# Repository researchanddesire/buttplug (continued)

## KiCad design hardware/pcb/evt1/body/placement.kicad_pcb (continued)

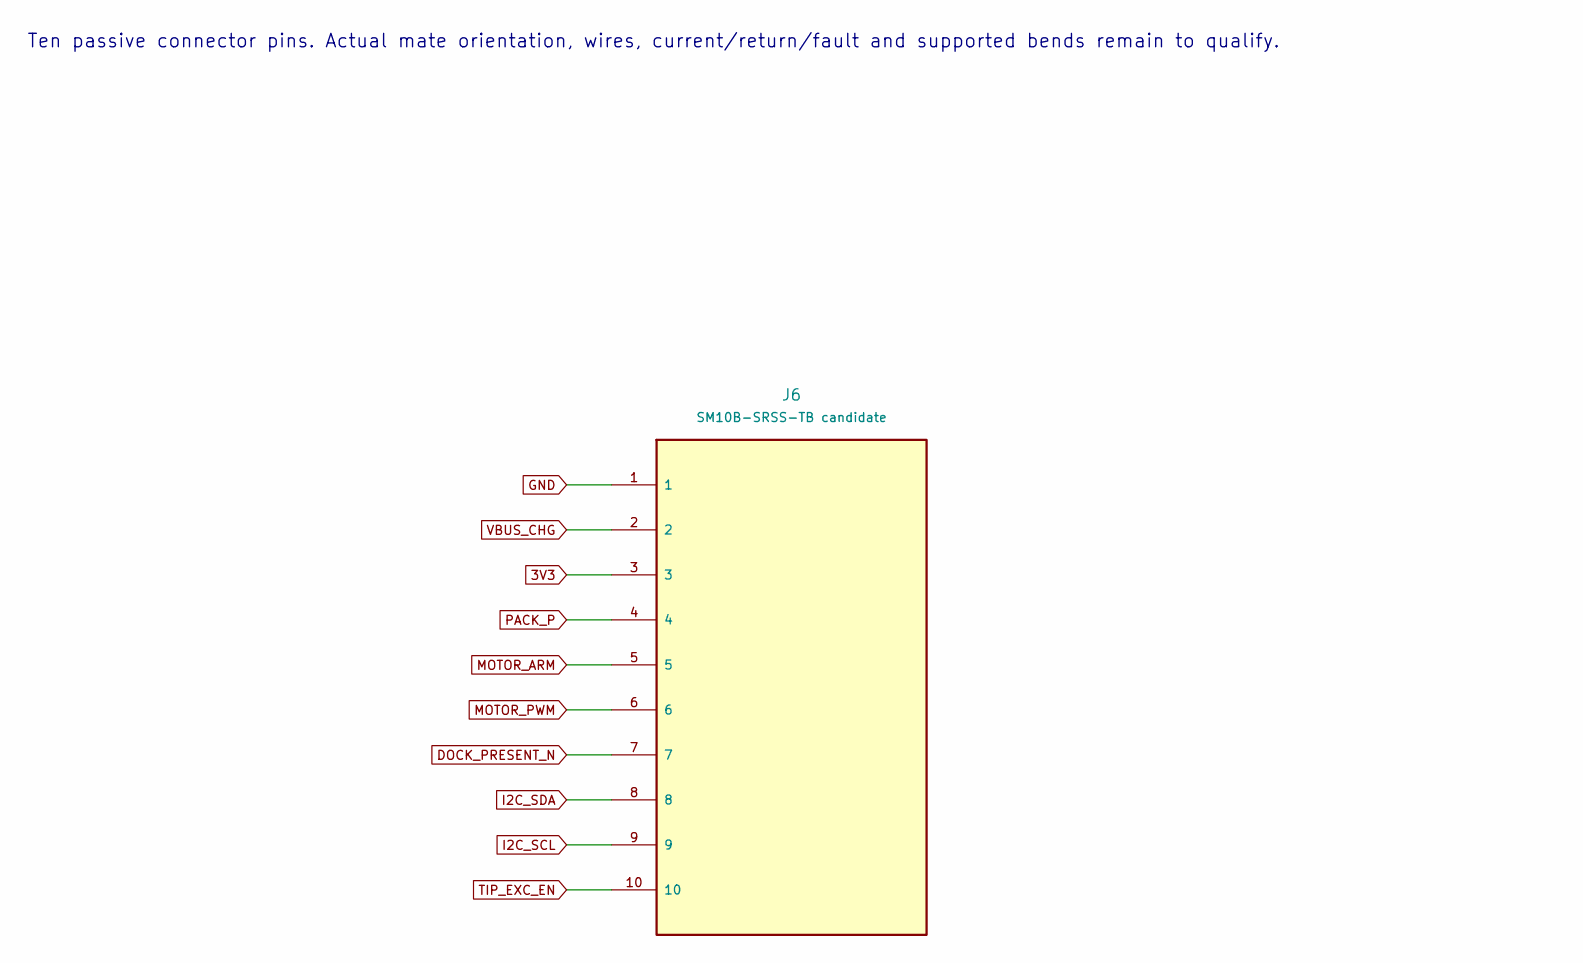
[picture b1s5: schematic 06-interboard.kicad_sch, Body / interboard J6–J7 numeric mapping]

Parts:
J6: SM10B-SRSS-TB candidate; JST_SH_SM10B-SRSS-TB_1x10-1MP_P1.00mm_Horizontal

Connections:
3V3: J6.3; also elsewhere on the board
DOCK_PRESENT_N: J6.7; also elsewhere on the board
GND: J6.1; also elsewhere on the board
I2C_SCL: J6.9; also elsewhere on the board
I2C_SDA: J6.8; also elsewhere on the board
MOTOR_ARM: J6.5; also elsewhere on the board
MOTOR_PWM: J6.6; also elsewhere on the board
PACK_P: J6.4; also elsewhere on the board
TIP_EXC_EN: J6.10; also elsewhere on the board
VBUS_CHG: J6.2; also elsewhere on the board

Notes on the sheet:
Ten passive connector pins. Actual mate orientation, wires, current/return/fault and supported bends remain to qualify.

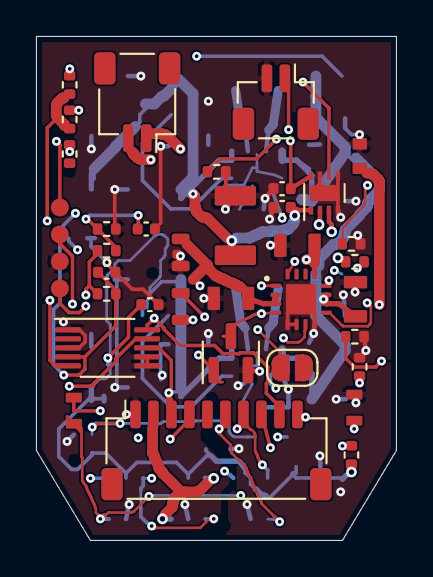
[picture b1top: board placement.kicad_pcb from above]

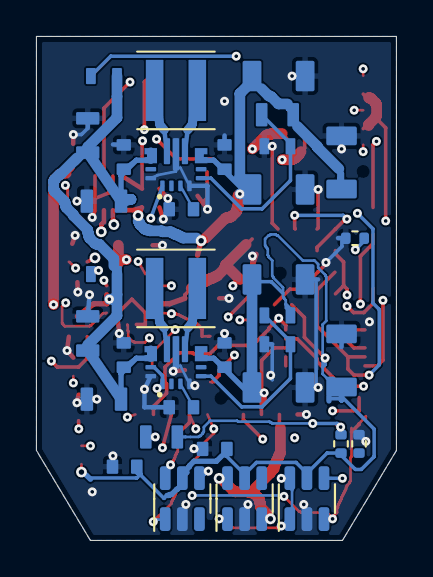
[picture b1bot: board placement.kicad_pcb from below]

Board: 6 copper layers, 20.0 x 28.0 mm, 69 parts (35 on the bottom side), 38 nets.

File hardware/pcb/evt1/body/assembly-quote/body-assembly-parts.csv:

Manufacturer,MPN,Quantity_per_board,References,Schematic_value,Footprint,Assembly_note,Manufacturer_source
Alpha and Omega Semiconductor,AO3400A,1,Q1,AO3400A,PrototypeR0:SOT-23,,https://www.aosmd.com/sites/default/files/res/datasheets/AO3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
Coilcraft,XFL4020-152MEC,2,L1 L2,1.5uH / Isat>=4A candidate,PrototypeR0:L_Coilcraft_XxL4020,Isat is specified at25C. Check transient/current/thermal behavior on assembled regulators; use manufacturer land pattern.,https://www.coilcraft.com/getmedia/50632d43-da1b-4cdb-8ab4-3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
JST,BM02B-SRSS-TB(LF)(SN),1,J5,TIP NTC / GND,EVT1:JST_SH_BM02B-SRSS-TB_1x02-1MP_P1.00mm_Vertical,Board header only. Order matching SHR housings/SSH terminals or qualified precrimp leads separately; flange ends are housed only after feeding free terminals through the neck.,https://www.jst-mfg.com/product/pdf/eng/eSH.pdf
JST,SM02B-SRSS-TB(LF)(SN),1,J3,MOTOR_2PIN,PrototypeR0:JST_SH_SM02B-SRSS-TB_1x02-1MP_P1.00mm_Horizontal,Board header only. Order matching SHR housings/SSH terminals or qualified precrimp leads separately; flange ends are housed only after feeding free terminals through the neck.,https://www.jst-mfg.com/product/pdf/eng/eSH.pdf
JST,SM10B-SRSS-TB(LF)(SN),1,J6,SM10B-SRSS-TB candidate,PrototypeR0:JST_SH_SM10B-SRSS-TB_1x10-1MP_P1.00mm_Horizontal,Board header only. Order matching SHR housings/SSH terminals or qualified precrimp leads separately; flange ends are housed only after feeding free terminals through the neck.,https://www.jst-mfg.com/product/pdf/eng/eSH.pdf
Murata,GRM155R71C104KA88D,3,C28 C29 C61,100nF,EVT1:C_0402_1005Metric; PrototypeR0:C_0402_1005Metric,,https://www.murata.com/en-global/api/pdfdownloadapi?cate=luC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
Murata,GRM155R71H103KA88D,2,C62 C63,10nF,EVT1:C_0402_1005Metric,,https://www.murata.com/en-global/api/pdfdownloadapi?cate=luC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
Murata,GRM188R71C104KA01D,5,C16 C26 C27 C43 C44,100nF; 100nF 10V,PrototypeR0:Murata_GRM18_0603_Reflow,,https://www.murata.com/en-global/api/pdfdownloadapi?cate=luC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
Murata,GRM21BR61A106KE19L,5,C11 C12 C21 C22 C3,10uF 10V,PrototypeR0:Murata_GRM21_0805_Reflow,,https://www.murata.com/en-global/api/pdfdownloadapi?cate=luC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
Murata,GRM21BR71A475KA73L,2,C1 C2,4.7uF 10V; 4.7uF 10V X7R,PrototypeR0:Murata_GRM21_0805_Reflow,,https://www.murata.com/en-global/api/pdfdownloadapi?cate=luC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
Murata,GRM31CR71A226KE15L,6,C13 C14 C15 C23 C24 C25,22uF 10V X7R,PrototypeR0:Murata_GRM31_1206_Reflow,,https://www.murata.com/en-global/api/pdfdownloadapi?cate=luC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
Murata,GRM32ER61A476KE20L,1,C30,47uF 10V,PrototypeR0:Murata_GRM32_1210_Reflow,,https://www.murata.com/en-global/api/pdfdownloadapi?cate=luC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
TDK,C1608X5R1A106K080AC,4,C51 C52 C53 C54,10uF 10V X5R 0603 HF,PrototypeR0:TDK_C1608_0603_Reflow,,https://product.tdk.com/en/search/capacitor/ceramic/mlcc/inf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
Texas Instruments,ADS1115IDGSR,1,U7,ADS1115IDGSR /0x48,EVT1:VSSOP-10_3x3mm_P0.5mm,,https://www.ti.com/lit/ds/symlink/ads1115.pdf
Texas Instruments,BQ24074RGTR,1,U1,BQ24074RGT candidate,PrototypeR0:TI_RGT0016C_3x3mm_BQ24074_EP1.68mm,,https://www.ti.com/lit/ds/symlink/bq24074.pdf
Texas Instruments,DRV8212DSGR,1,U5,DRV8212DSG candidate,PrototypeR0:WSON-8-1EP_2x2mm_P0.5mm_EP0.9x1.6mm,,https://www.ti.com/lit/ds/symlink/drv8212.pdf
Texas Instruments,SN74LVC1G11DBVR,1,U4,SN74LVC1G11DBV candidate,PrototypeR0:SOT-23-6,,https://www.ti.com/lit/ds/symlink/sn74lvc1g11.pdf
Texas Instruments,TPS3700DDCR,1,U8,TPS3700DDCR,PrototypeR0:TSOT-23-6,,https://www.ti.com/lit/ds/symlink/tps3700.pdf
Texas Instruments,TPS3808G33DBVR,1,U9,TPS3808G33DBVR,PrototypeR0:SOT-23-6,,https://www.ti.com/lit/ds/symlink/tps3808.pdf
Texas Instruments,TPS63070RNMR,2,U2 U3,TPS63070RNM candidate,PrototypeR0:TI_RNM0015A_2.5x3mm_TPS63070,,https://www.ti.com/lit/ds/symlink/tps63070.pdf
Vishay,TNPW0402100KBEED,4,R23 R24 R25 R48,100k; 100k 1%,PrototypeR0:R_0402_1005Metric,,https://www.vishay.com/docs/28758/tnpw_e3.pdf
Vishay,TNPW040210K0BEED,7,R3 R4 R42 R5 R61 R62 R63,10.0k 0.1%; 10k; 10k 0.1%,EVT1:R_0402_1005Metric; PrototypeR0:R_0402_1005Metric,,https://www.vishay.com/docs/28758/tnpw_e3.pdf
Vishay,TNPW040211K0BEED,1,R46,11k 1%,PrototypeR0:R_0402_1005Metric,,https://www.vishay.com/docs/28758/tnpw_e3.pdf
Vishay,TNPW04021K00BEED,1,R47,1k 1%,PrototypeR0:R_0402_1005Metric,,https://www.vishay.com/docs/28758/tnpw_e3.pdf
Vishay,TNPW04023K24BEED,1,R2,3.24k 1%,PrototypeR0:R_0402_1005Metric,,https://www.vishay.com/docs/28758/tnpw_e3.pdf
Vishay,TNPW04028K87BEED,1,R1,8.87k 1% / ~100mA,PrototypeR0:R_0402_1005Metric,,https://www.vishay.com/docs/28758/tnpw_e3.pdf
Vishay,TNPW0603100KBEEA,2,R12 R22,100k 0.1%,PrototypeR0:Vishay_TNPW0603_IEC_Reflow,,https://www.vishay.com/docs/28758/tnpw_e3.pdf
Vishay,TNPW060310K0BEEA,2,R13 R26,10k,PrototypeR0:Vishay_TNPW0603_IEC_Reflow,,https://www.vishay.com/docs/28758/tnpw_e3.pdf
Vishay,TNPW0603110KBEEA,1,R44,110k 0.1%,PrototypeR0:Vishay_TNPW0603_IEC_Reflow,,https://www.vishay.com/docs/28758/tnpw_e3.pdf
Vishay,TNPW0603200KBEEA,1,R45,200k 0.1%,PrototypeR0:Vishay_TNPW0603_IEC_Reflow,,https://www.vishay.com/docs/28758/tnpw_e3.pdf
Vishay,TNPW0603312KBEEA,1,R11,312k 0.1%,PrototypeR0:Vishay_TNPW0603_IEC_Reflow,,https://www.vishay.com/docs/28758/tnpw_e3.pdf
Vishay,TNPW0805362KBEEA,1,R21,362k 0.1%,PrototypeR0:Vishay_TNPW0805_IEC_Reflow,,https://www.vishay.com/docs/28758/tnpw_e3.pdf
Vishay,TNPW0805715KBEEA,1,R43,715k 0.1%,PrototypeR0:Vishay_TNPW0805_IEC_Reflow,,https://www.vishay.com/docs/28758/tnpw_e3.pdf

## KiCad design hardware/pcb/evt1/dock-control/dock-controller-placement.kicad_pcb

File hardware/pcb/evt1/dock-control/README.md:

# Dock controller and lid UI — EVT candidate

Open `dock-control.kicad_sch` for the two-sheet native circuit. The source,
hardware safety and UV circuits are sibling folders; the merged review circuit
is in `../dock-system/`. These files are not fabrication artwork.

- STM32L071CBT6: all 48 physical pins, internal 4.2 MHz MSI, SWD/BOOT recovery,
  hardware reset/watchdog interfaces, analog NTC inputs and ADS1115 monitors.
- Newhaven NHD-C12864B2Z-RN-FBW: actual 27-pin 8080 interface and charge-pump
  circuit, write-only `/RD`, twelve source resistors, internal contrast commands.
- Three Omron B3FS-1002P switches. CENTER goes to the independent safety
  debouncer; the MCU reads its output and cannot create the hardware start edge.
- Hirose FH12-20S-0.5SH(55) hinge sockets and Molex 0151660220 opposite-face
  ultra-flex cable. UV power uses its separate harness, not this 20-way cable.
- Molex 52437-2771 LCD socket is an **EVT mating-trial selection**. The LCD's
  exposed/stiffened tail lengths differ from the socket recommendation.

`pin-contract.json` binds physical MCU/LCD/connector pins and signal roles.
`parts-selection.json` lists selected positions and source links; it does not
replace the human-owned product BOM. `native-checks.json` binds native ERC and
exported terminal checks to source hashes. Standalone lid ERC has two visible
external-supply context findings; the two-sheet hierarchy has zero errors and
warnings without exclusions. Full dock integration and powered tests remain open.

## Placement sources

`dock-controller-placement.kicad_pcb` is only the 44-reference controller subset
on a **shared** source/controller/safety base outline. It reserves the source
zone at Y0..25 and the safety zone X15..45/Y30..60. Source and safety components
must be placed on this same board; do not stack three complete boards. Two
8×8 mm contact-carrier openings contain a full 7×7 mm clear square, with 0.5 mm
corner chamfers. The front USB nose and final mounting/port details remain DFM work.

`dock-lid-placement.kicad_pcb` places 28 references with the switches at dock
X−22/0/+22, Y54. A native keepout protects the central flex return corridor.
J302's X/Y position is a candidate pad-row location, **not the LCD tip** or a
solved connector mate. The board's installed Z is deliberately unresolved.
Both candidates have zero tracks/vias and remain unrouted.

Native saved-board checks cover 274 physical pad instances. Native KiCad 10.0.8
placement DRC reports zero geometry/library violations, with 99 base and 80 lid
unconnected groups expected before routing. This is not a completed DRC or
fabrication release. The independent firmware folder has a separate PCB audit.

## Coordinate and connector conventions

The native board frame is `dockX = pcbX − 100`, `dockY = 200 − pcbY`.
For StepUp `pcb_placement=2`, the outline-centred MCAD frame is right handed:
F.Cu is local Z0, B.Cu Z−1, and MCAD Y already reflects KiCad's down-page Y.
The rigid FreeCAD placement is an identity rotation plus the translations in
each `*-placement.json`: base `(0,32,6.4)`; lid `(0,84.5,Z_UNRESOLVED)`.
The actual import must be checked against these datums before assembly fit.

- J302 at native 0°: mouth dock−Y, pin1 dock−X. The installed LCD's fold about
  X preserves pin1 at−X; **LCD pin p connects directly to socket pad p**.
  Manufacturer SD-52437-019 Rev F top view and mounting-side land pattern,
  plus an independent audit, support this mapping. No 180° Z rotation applies.
- J201/J301 at native 180°: both mouths dock+Y and both pin1 sides dock+X.
  The intended opposite-face cable route preserves conductor p→p. Actual
  closed/open routing, continuity and hinge life remain to be tested.

The installed LCD tip centre is `(0,112.575222039,61.85)`; its actual contact
face is Z61.70, normal−Z. Copper spans Z61.70..61.80, flex Z61.80..61.90 and
stiffener Z61.90..62.00. Molex's sectional reference dimensions show 3 mm
insertion depth and 1.7 mm from the **inserted tip** to the contact point.
The drawing's 0.82 mm exterior side-feature datum is not a qualified contact
plane. No socket height or insertion mate is inferred from it. Manufacturer
STEP retrieval failed; J302 has no substitute box model and remains an explicit
missing 3D reference. Its contact height, actual seating and tail compatibility
need manufacturer geometry/acceptance or a received-parts trial before power.

## Rebuild and check

Use ordinary Python for `build_source.py`, then `check_native.py --kicad-cli
PATH_TO_KICAD10`. Exports/ERC run sequentially. Source construction refreshes
the native circuit and local selected footprint/model snapshots.

Use KiCad7's bundled Python with `wx.App(False)` for each placement operation:

```sh
python build_placement.py controller
python build_placement.py lid
python check_placement.py controller
python check_placement.py lid
```

Run one board per process. `--restart-placement` permits replacement only of
this builder's unchanged, unrouted candidate; preserve edited/routed work first.
`check_models.py` runs in FreeCAD Python and checks native BRep validity and
exact bounds after coarse tessellation. The nine local library STEP models
describe actual standard external cases, terminals and actuators, not component
maximum-tolerance proofs. `model-provenance.json` and the local KiCad license
record their origins. No physical fit, USB/programming, UV output, dose,
cleaning efficacy, thermal/leakage result or full-product order release follows.

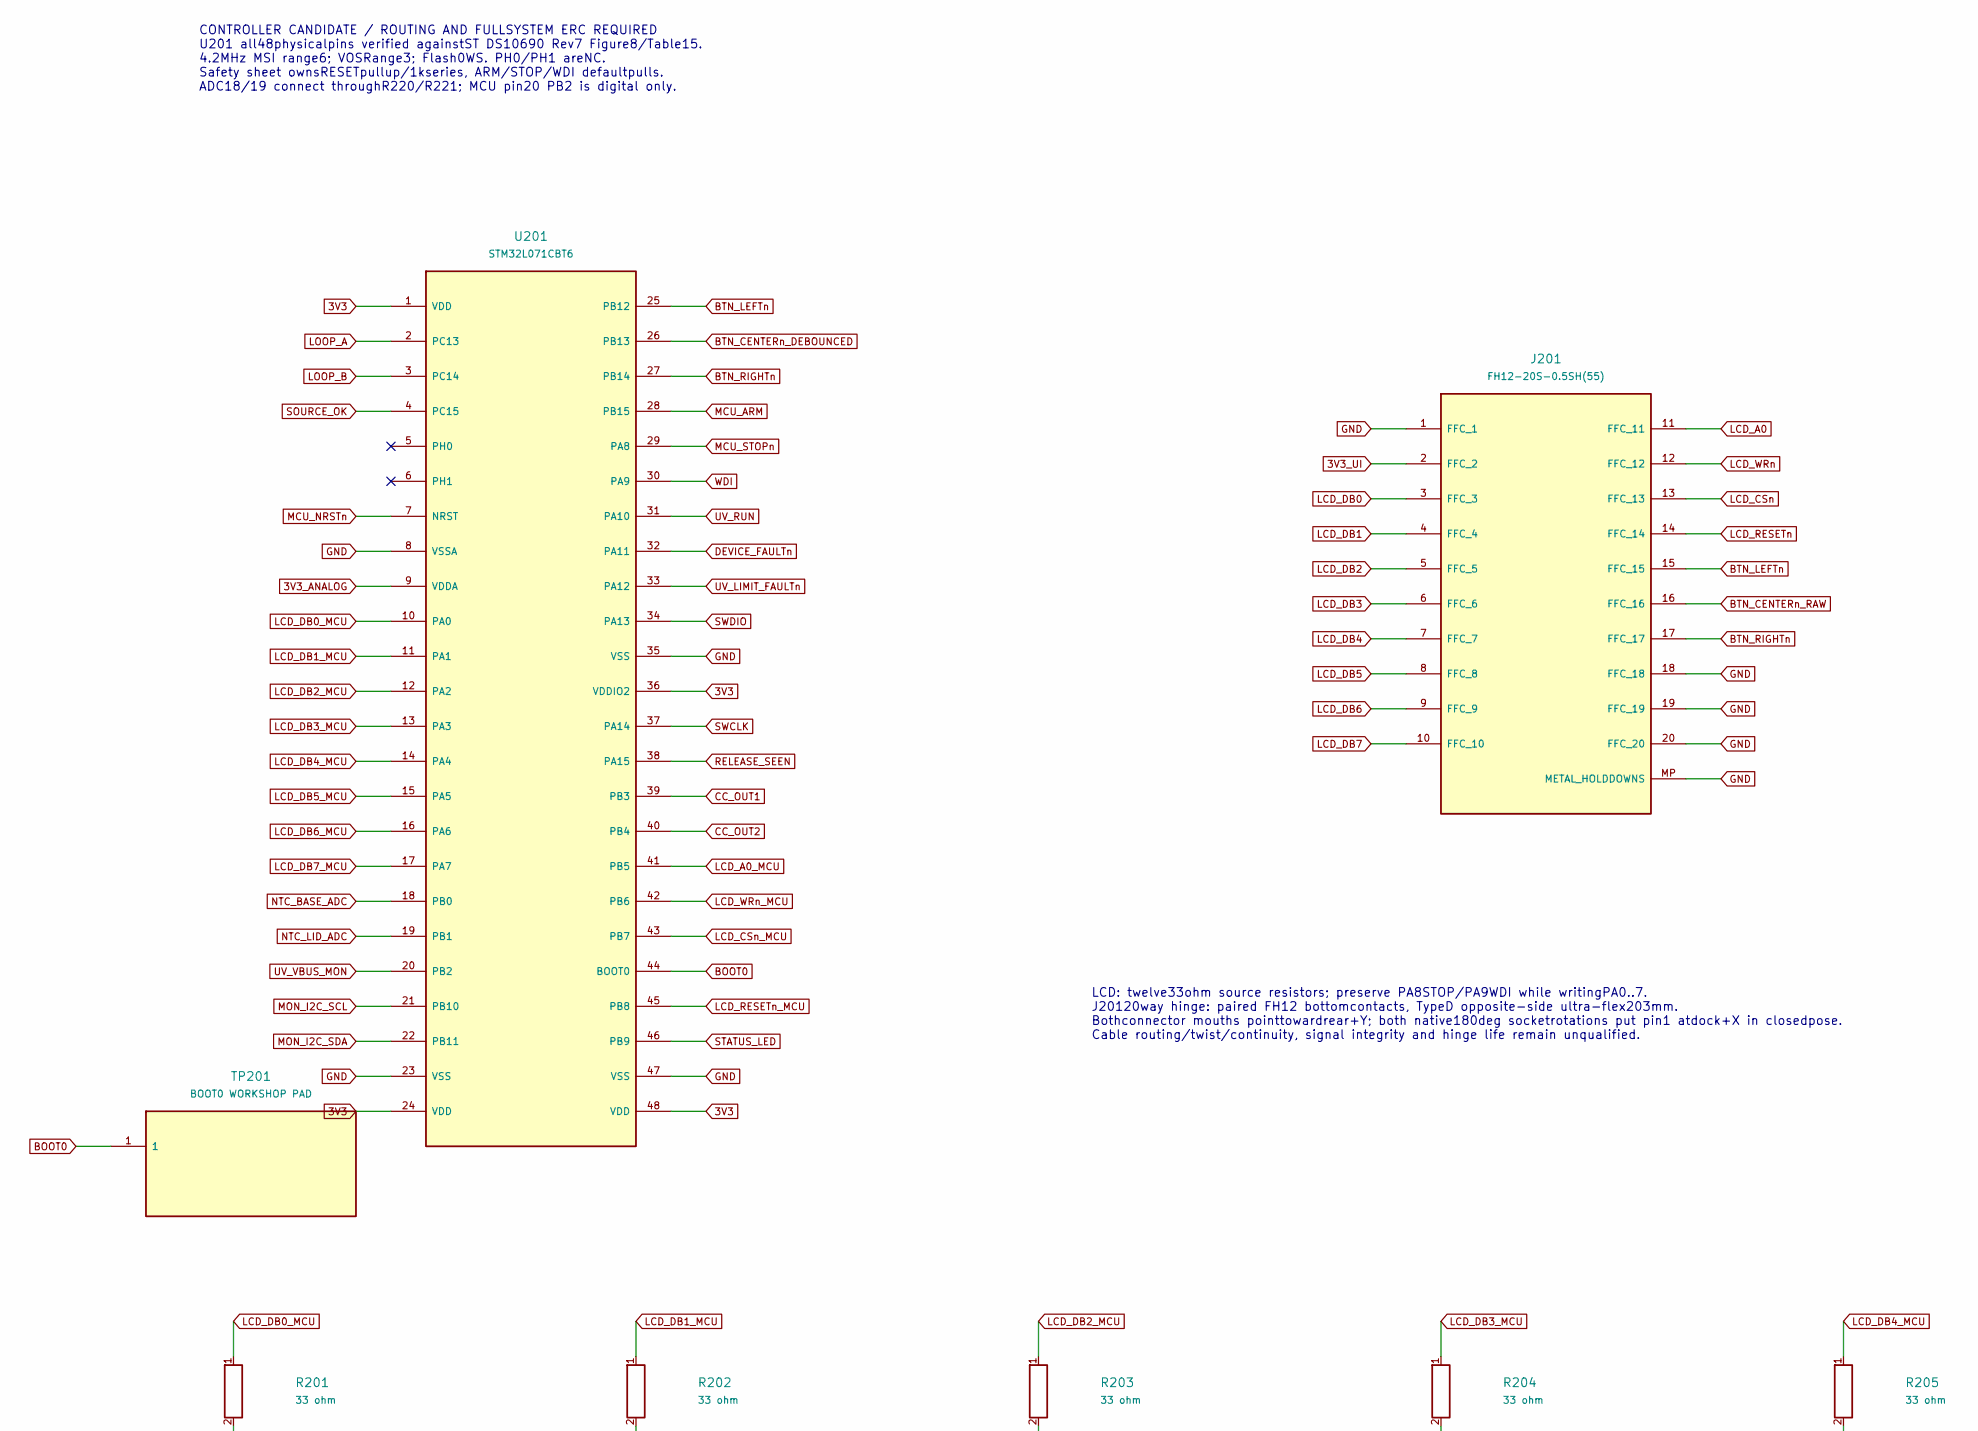
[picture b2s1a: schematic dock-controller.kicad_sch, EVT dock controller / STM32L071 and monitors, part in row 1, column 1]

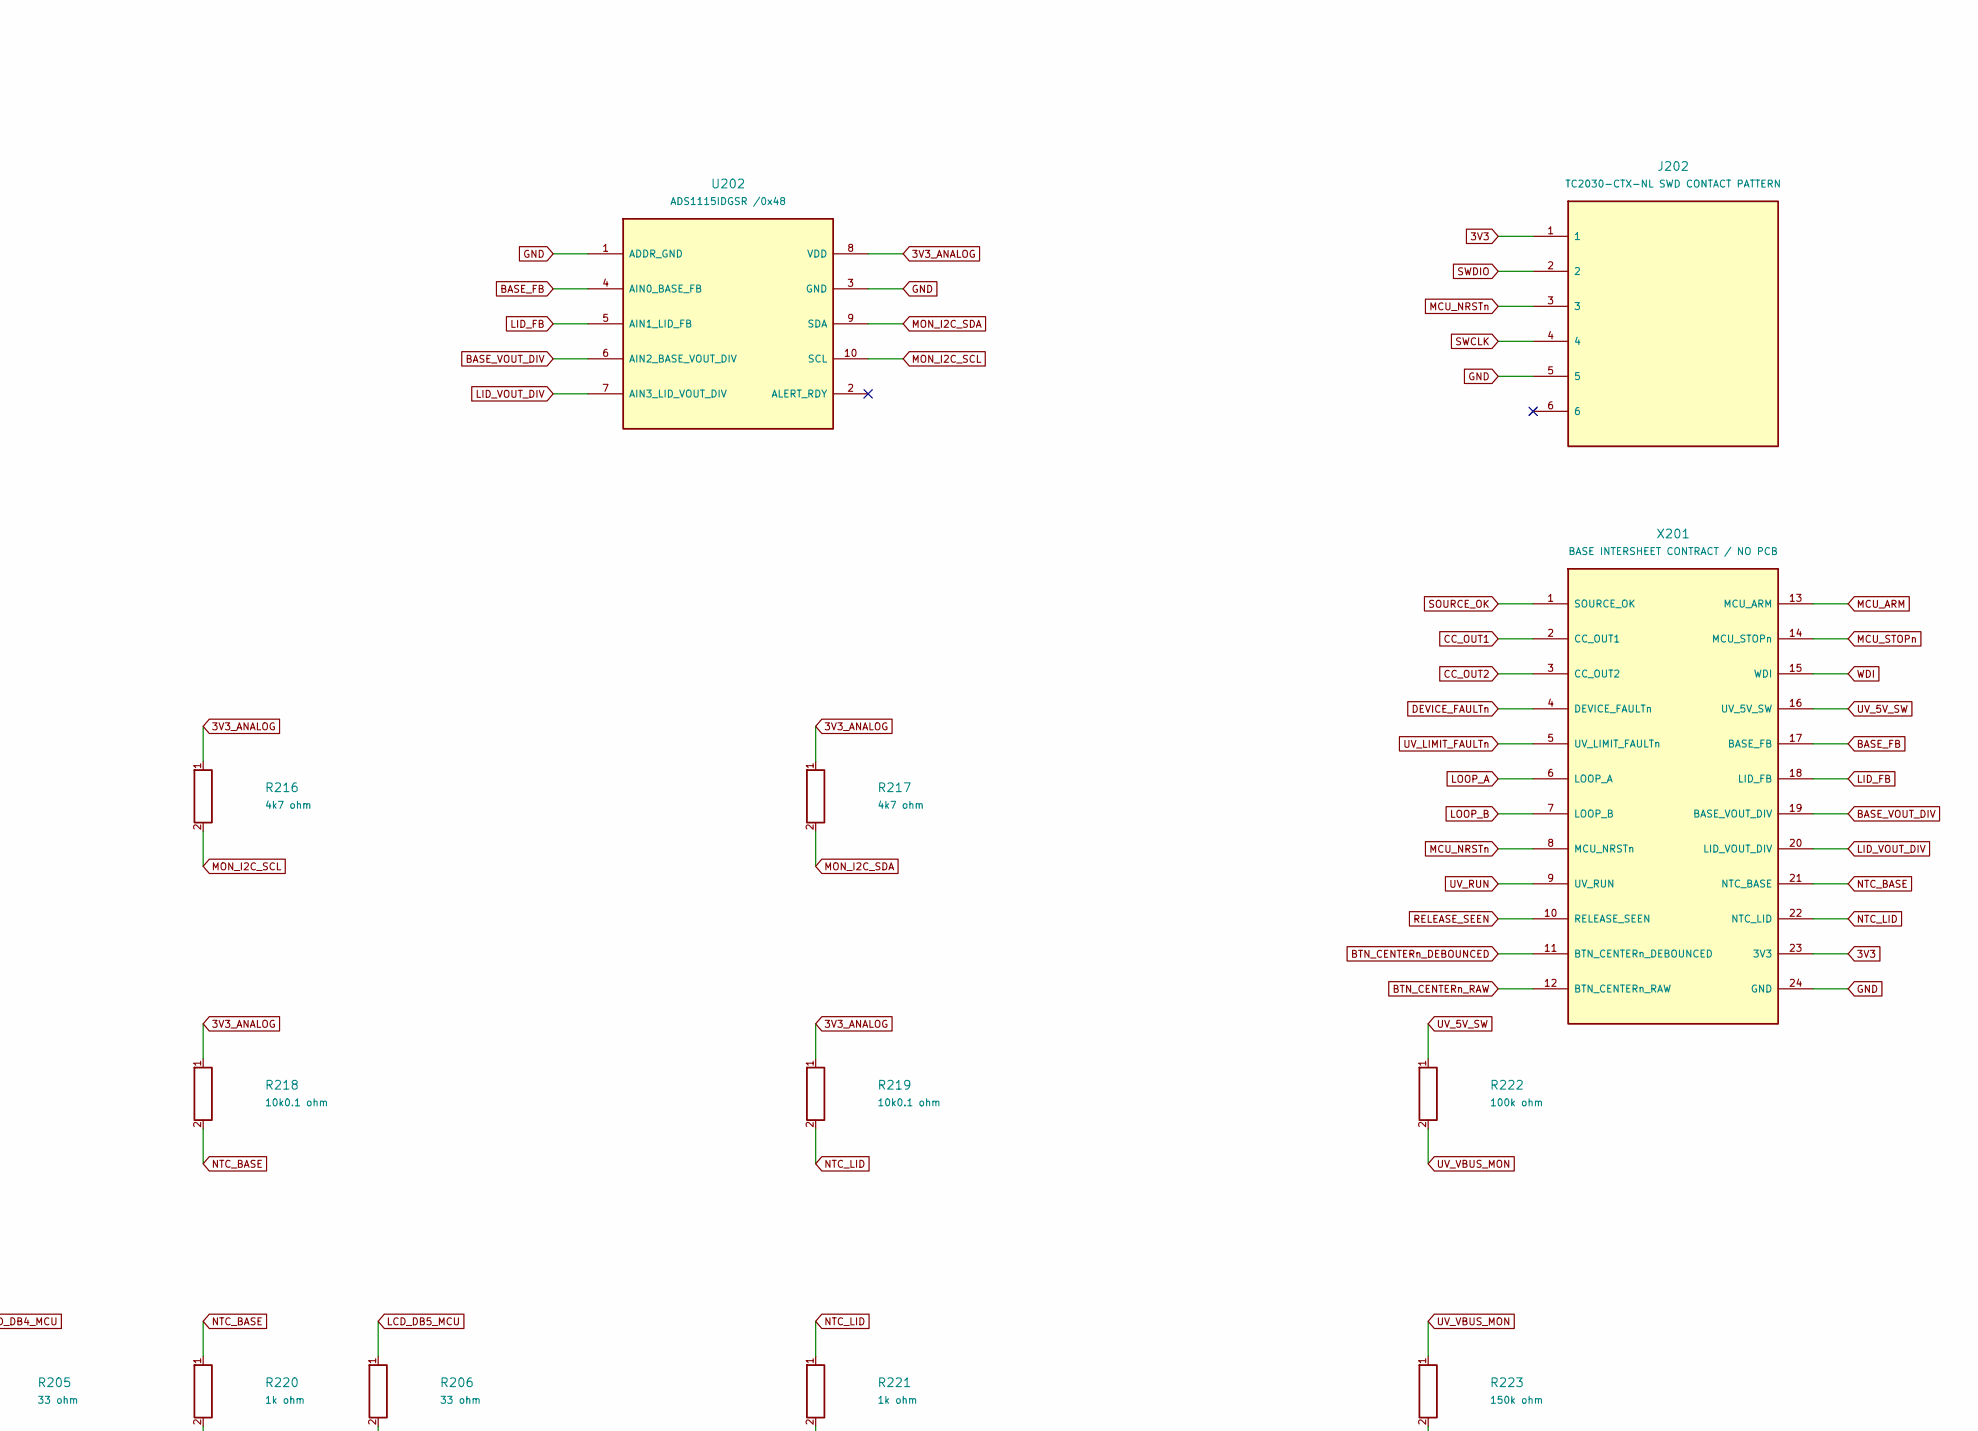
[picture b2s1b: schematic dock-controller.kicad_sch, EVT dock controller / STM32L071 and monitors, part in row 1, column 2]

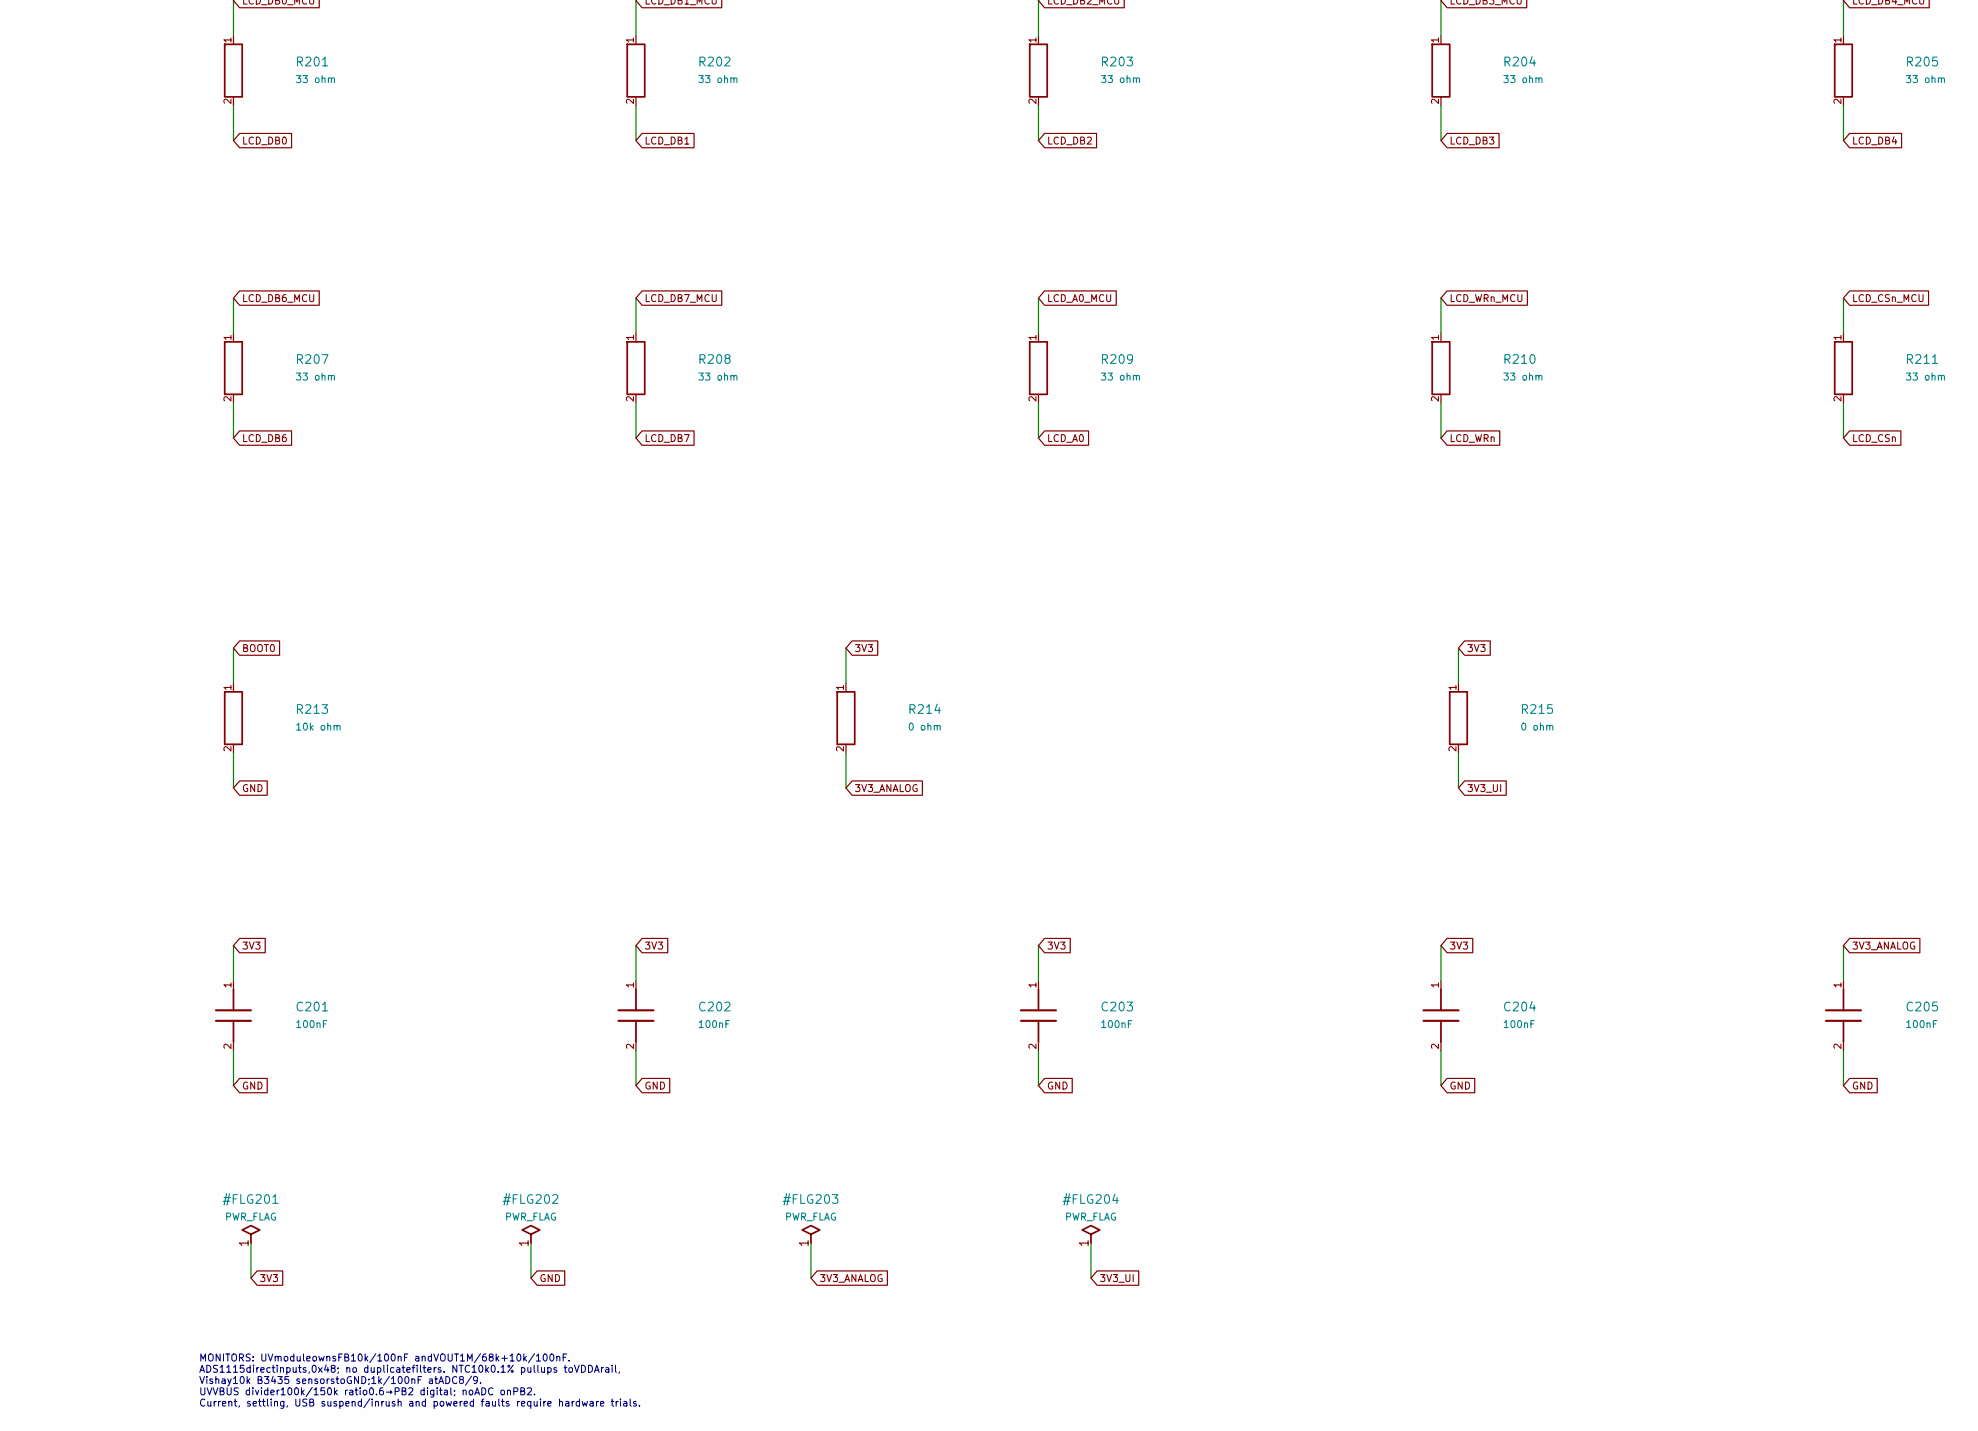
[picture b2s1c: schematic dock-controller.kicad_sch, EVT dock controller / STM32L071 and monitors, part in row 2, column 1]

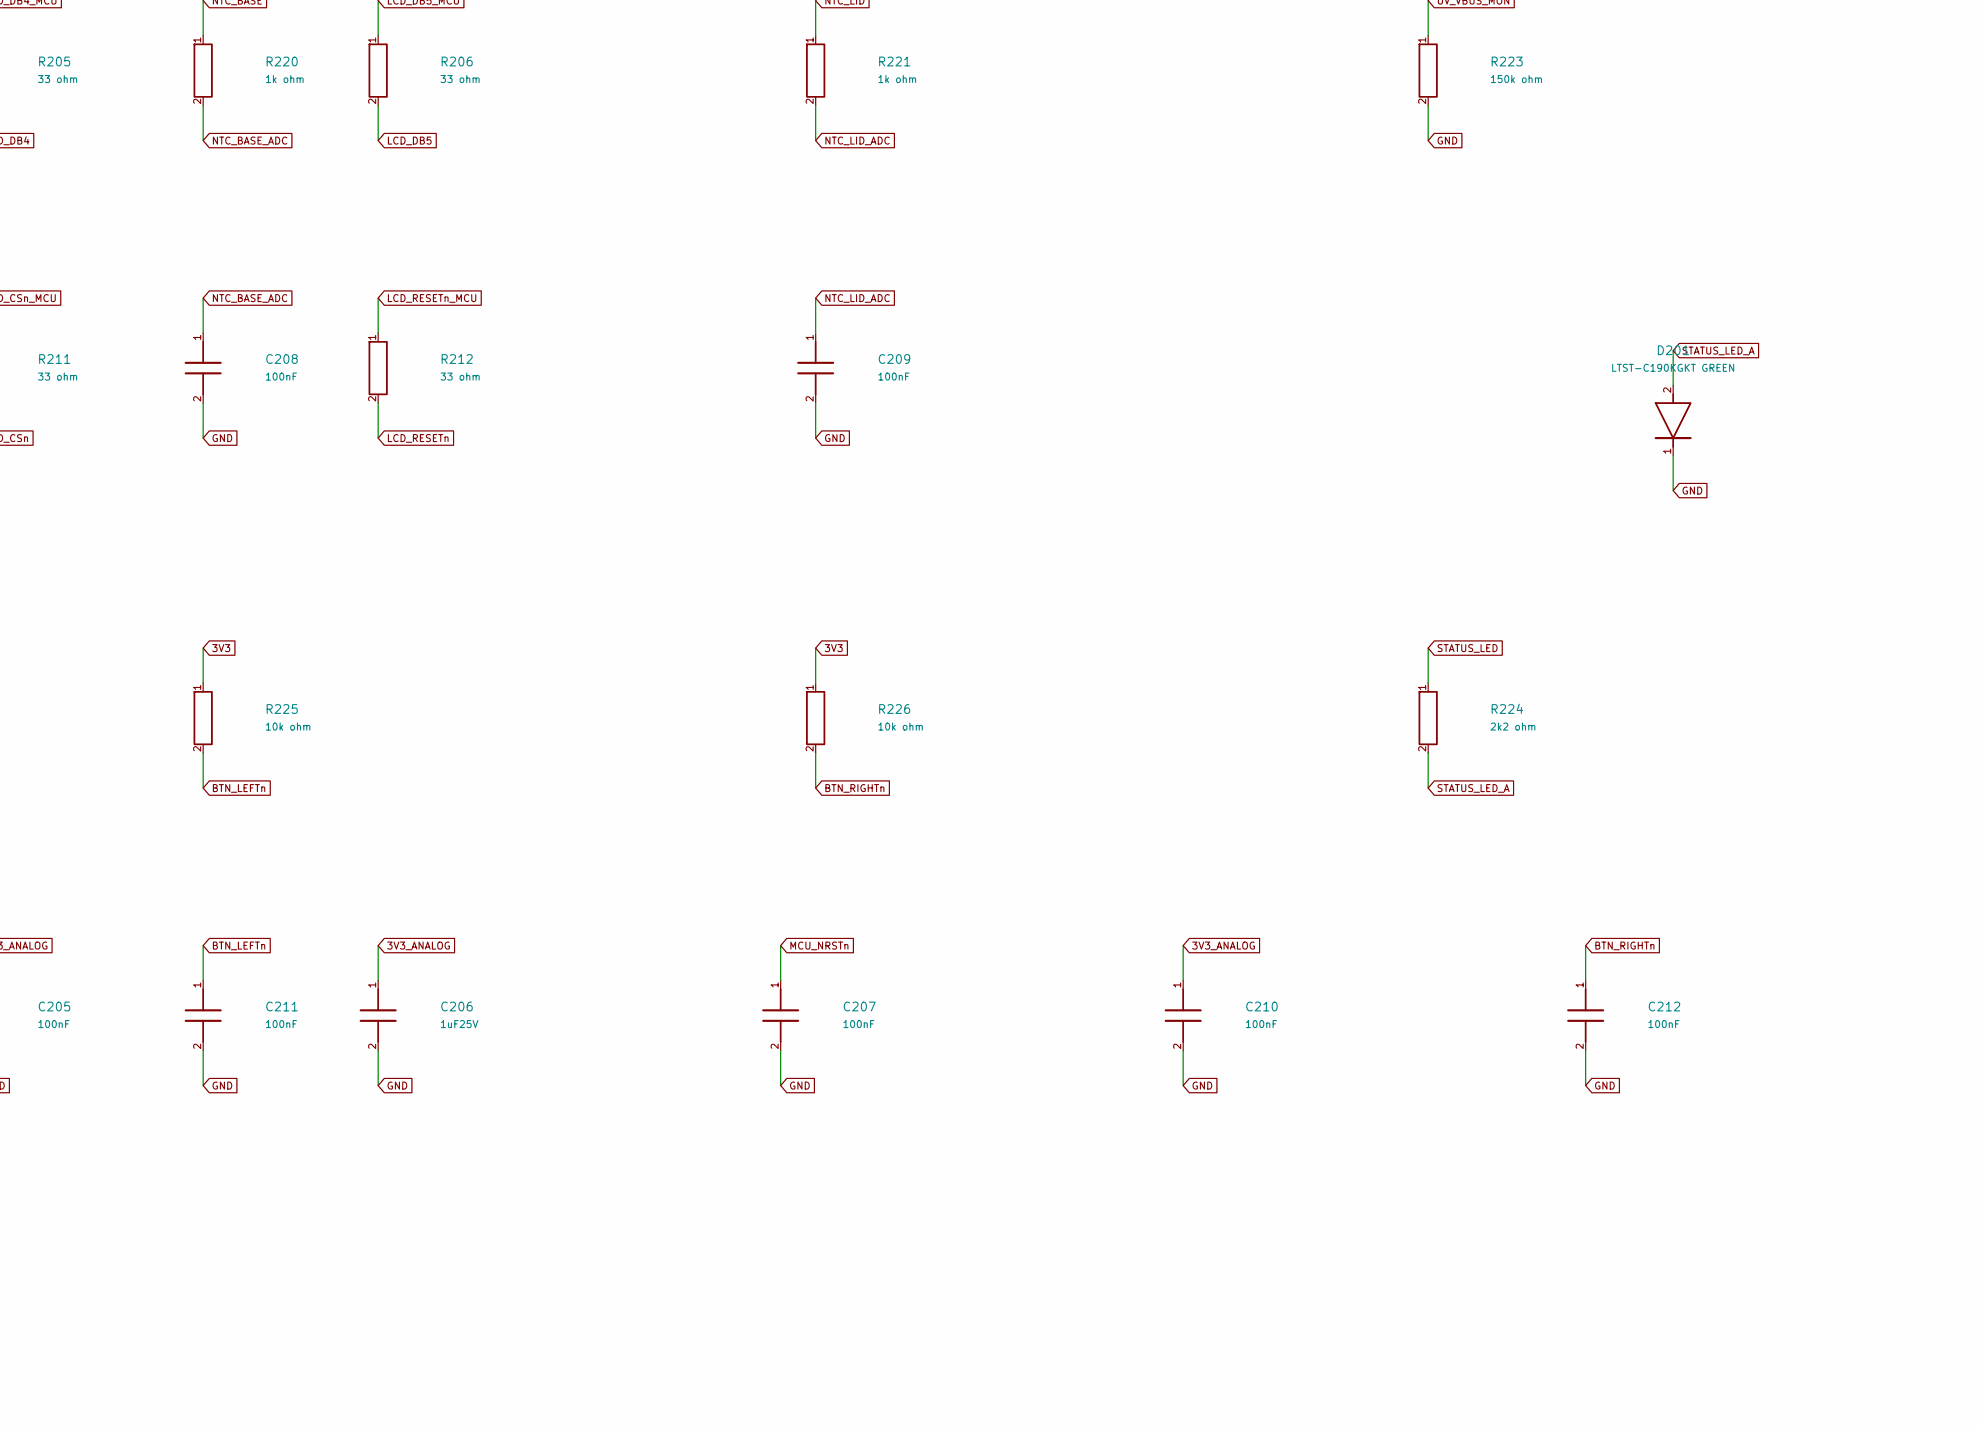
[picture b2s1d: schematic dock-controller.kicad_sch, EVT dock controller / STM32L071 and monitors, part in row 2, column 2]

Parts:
C201, C202, C203, C204, C205, C207, C208, C209, C210, C211, C212: 100nF; C_0402_1005Metric; MPN GRM155R71C104KA88D
C206: 1uF25V; C_0603_1608Metric; MPN C1608X7R1E105K080AB
D201: LTST-C190KGKT GREEN; LED_0603_1608Metric; MPN LTST-C190KGKT
J201: FH12-20S-0.5SH(55); Hirose_FH12-20S-0.5SH_1x20-1MP_P0.50mm_Horizontal; MPN FH12-20S-0.5SH(55)
J202: TC2030-CTX-NL SWD CONTACT PATTERN; Tag-Connect_TC2030-IDC-NL_2x03_P1.27mm_Vertical; MPN –
R201, R202, R203, R204, R205, R206, R207, R208, R209, R210, R211, R212: 33 ohm; R_0603_1608Metric; MPN RC0603FR-0733RL
R213, R225, R226: 10k ohm; R_0603_1608Metric; MPN RC0603FR-0710KL
R214, R215: 0 ohm; R_0603_1608Metric; MPN RC0603JR-070RL
R216, R217: 4k7 ohm; R_0603_1608Metric; MPN RC0603FR-074K7L
R218, R219: 10k0.1 ohm; R_0603_1608Metric; MPN RT0603BRD0710KL
R220, R221: 1k ohm; R_0603_1608Metric; MPN RC0603FR-071KL
R222: 100k ohm; R_0603_1608Metric; MPN RC0603FR-07100KL
R223: 150k ohm; R_0603_1608Metric; MPN RC0603FR-07150KL
R224: 2k2 ohm; R_0603_1608Metric; MPN RC0603FR-072K2L
TP201: BOOT0 WORKSHOP PAD; TestPoint_Pad_D1.0mm; MPN –
U201: STM32L071CBT6; LQFP-48_7x7mm_P0.5mm; MPN STM32L071CBT6
U202: ADS1115IDGSR /0x48; VSSOP-10_3x3mm_P0.5mm; MPN ADS1115IDGSR
X201: BASE INTERSHEET CONTRACT / NO PCB; MPN –

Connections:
3V3: C201.1, C202.1, C203.1, C204.1, J202.1, R214.1, R215.1, R225.1, R226.1, U201.1 (VDD), U201.24 (VDD), U201.36 (VDDIO2), U201.48 (VDD), X201.23 (3V3)
3V3_ANALOG: C205.1, C206.1, C210.1, R214.2, R216.1, R217.1, R218.1, R219.1, U201.9 (VDDA), U202.8 (VDD)
3V3_UI: J201.2 (FFC_2), R215.2
BASE_FB: U202.4 (AIN0_BASE_FB), X201.17 (BASE_FB)
BASE_VOUT_DIV: U202.6 (AIN2_BASE_VOUT_DIV), X201.19 (BASE_VOUT_DIV)
BOOT0: R213.1, TP201.1, U201.44 (BOOT0)
BTN_CENTERn_DEBOUNCED: U201.26 (PB13), X201.11 (BTN_CENTERn_DEBOUNCED)
BTN_CENTERn_RAW: J201.16 (FFC_16), X201.12 (BTN_CENTERn_RAW)
BTN_LEFTn: C211.1, J201.15 (FFC_15), R225.2, U201.25 (PB12)
BTN_RIGHTn: C212.1, J201.17 (FFC_17), R226.2, U201.27 (PB14)
CC_OUT1: U201.39 (PB3), X201.2 (CC_OUT1)
CC_OUT2: U201.40 (PB4), X201.3 (CC_OUT2)
DEVICE_FAULTn: U201.32 (PA11), X201.4 (DEVICE_FAULTn)
GND: C201.2, C202.2, C203.2, C204.2, C205.2, C206.2, C207.2, C208.2, C209.2, C210.2, C211.2, C212.2, D201.1 (2), J201.1 (FFC_1), J201.18 (FFC_18), J201.19 (FFC_19), J201.20 (FFC_20), J201.MP (METAL_HOLDDOWNS), J202.5, R213.2, R223.2, U201.8 (VSSA), U201.23 (VSS), U201.35 (VSS), U201.47 (VSS), U202.1 (ADDR_GND), U202.3 (GND), X201.24 (GND)
LCD_A0: J201.11 (FFC_11), R209.2
LCD_A0_MCU: R209.1, U201.41 (PB5)
LCD_CSn: J201.13 (FFC_13), R211.2
LCD_CSn_MCU: R211.1, U201.43 (PB7)
LCD_DB0: J201.3 (FFC_3), R201.2
LCD_DB0_MCU: R201.1, U201.10 (PA0)
LCD_DB1: J201.4 (FFC_4), R202.2
LCD_DB1_MCU: R202.1, U201.11 (PA1)
LCD_DB2: J201.5 (FFC_5), R203.2
LCD_DB2_MCU: R203.1, U201.12 (PA2)
LCD_DB3: J201.6 (FFC_6), R204.2
LCD_DB3_MCU: R204.1, U201.13 (PA3)
LCD_DB4: J201.7 (FFC_7), R205.2
LCD_DB4_MCU: R205.1, U201.14 (PA4)
LCD_DB5: J201.8 (FFC_8), R206.2
LCD_DB5_MCU: R206.1, U201.15 (PA5)
LCD_DB6: J201.9 (FFC_9), R207.2
LCD_DB6_MCU: R207.1, U201.16 (PA6)
LCD_DB7: J201.10 (FFC_10), R208.2
LCD_DB7_MCU: R208.1, U201.17 (PA7)
LCD_RESETn: J201.14 (FFC_14), R212.2
LCD_RESETn_MCU: R212.1, U201.45 (PB8)
LCD_WRn: J201.12 (FFC_12), R210.2
LCD_WRn_MCU: R210.1, U201.42 (PB6)
LID_FB: U202.5 (AIN1_LID_FB), X201.18 (LID_FB)
LID_VOUT_DIV: U202.7 (AIN3_LID_VOUT_DIV), X201.20 (LID_VOUT_DIV)
LOOP_A: U201.2 (PC13), X201.6 (LOOP_A)
LOOP_B: U201.3 (PC14), X201.7 (LOOP_B)
MCU_ARM: U201.28 (PB15), X201.13 (MCU_ARM)
MCU_NRSTn: C207.1, J202.3, U201.7 (NRST), X201.8 (MCU_NRSTn)
MCU_STOPn: U201.29 (PA8), X201.14 (MCU_STOPn)
MON_I2C_SCL: R216.2, U201.21 (PB10), U202.10 (SCL)
MON_I2C_SDA: R217.2, U201.22 (PB11), U202.9 (SDA)
NTC_BASE: R218.2, R220.1, X201.21 (NTC_BASE)
NTC_BASE_ADC: C208.1, R220.2, U201.18 (PB0)
NTC_LID: R219.2, R221.1, X201.22 (NTC_LID)
NTC_LID_ADC: C209.1, R221.2, U201.19 (PB1)
RELEASE_SEEN: U201.38 (PA15), X201.10 (RELEASE_SEEN)
SOURCE_OK: U201.4 (PC15), X201.1 (SOURCE_OK)
STATUS_LED: R224.1, U201.46 (PB9)
STATUS_LED_A: D201.2 (1), R224.2
SWCLK: J202.4, U201.37 (PA14)
SWDIO: J202.2, U201.34 (PA13)
UV_5V_SW: R222.1, X201.16 (UV_5V_SW)
UV_LIMIT_FAULTn: U201.33 (PA12), X201.5 (UV_LIMIT_FAULTn)
UV_RUN: U201.31 (PA10), X201.9 (UV_RUN)
UV_VBUS_MON: R222.2, R223.1, U201.20 (PB2)
WDI: U201.30 (PA9), X201.15 (WDI)

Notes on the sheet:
CONTROLLER CANDIDATE / ROUTING AND FULLSYSTEM ERC REQUIRED U201 all48physicalpins verified againstST DS10690 Rev7 Figure8/Table15. 4.2MHz MSI range6; VOSRange3; Flash0WS. PH0/PH1 areNC. Safety sheet ownsRESETpullup/1kseries, ARM/STOP/WDI defaultpulls. ADC18/19 connect throughR220/R221; MCU pin20 PB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
LCD: twelve33ohm source resistors; preserve PA8STOP/PA9WDI while writingPA0..7. J20120way hinge: paired FH12 bottomcontacts, TypeD opposite-side ultra-flex203mm. Bothconnector mouths pointtowardrear+Y; both native180deg socketrotations put pin1 atdock+X in closedpose. Cable routing/twist/continuity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
MONITORS: UVmoduleownsFB10k/100nF andVOUT1M/68k+10k/100nF. ADS1115directinputs,0x48; no duplicatefilters. NTC10k0.1% pullups toVDDArail, Vishay10k B3435 sensorstoGND;1k/100nF atADC8/9. UVVBUS divider100k/150k ratio0.6→PB2 digital; noADC onPB2. Current, settling, USB suspend/inrush and powered fault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

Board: 2 copper layers, 44 parts (0 on the bottom side), 43 nets, no tracks yet.
